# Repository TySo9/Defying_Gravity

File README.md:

# Defying_Gravity
Repository for University Kentucky Senior Capstone Design Team (Spring/Fall 2021), Defying Gravity.

## iOS App
  - Written in C# for potential multi-platform support in the future
  - Designed for iPad
  - Controls the ESP32 via Wi-Fi
  
## ESP32
  - Written in Arduino C
  - Controls motors, sensors, etc on the platform
  - Controlled by iOS App via Wi-Fi

## 3D Drawings
  - Files for the 3D printed parts of the device
     - Left Brake "Pads"
     - Right Brake "Pads"
     - Washer (?)

## 3D Drawings (KiCAD)
  - Files for PCB

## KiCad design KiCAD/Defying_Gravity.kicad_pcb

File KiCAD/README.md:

PCB Design Files for KiCAD

Because we decided to build a perfboard based on the Schematic for time, testing, and budget purposes, the PCB itself is unfinished. The Schematic, Ratnest, Part Selection, Footprint Design/Selection, etc.. is all finished. Since all the groundwork is complete, all the next person has to do is move around the footprints, connect the ratnest, and generate Gerbers. Should be quick and easy. I recommend using PCBWay to fabricate the boards.

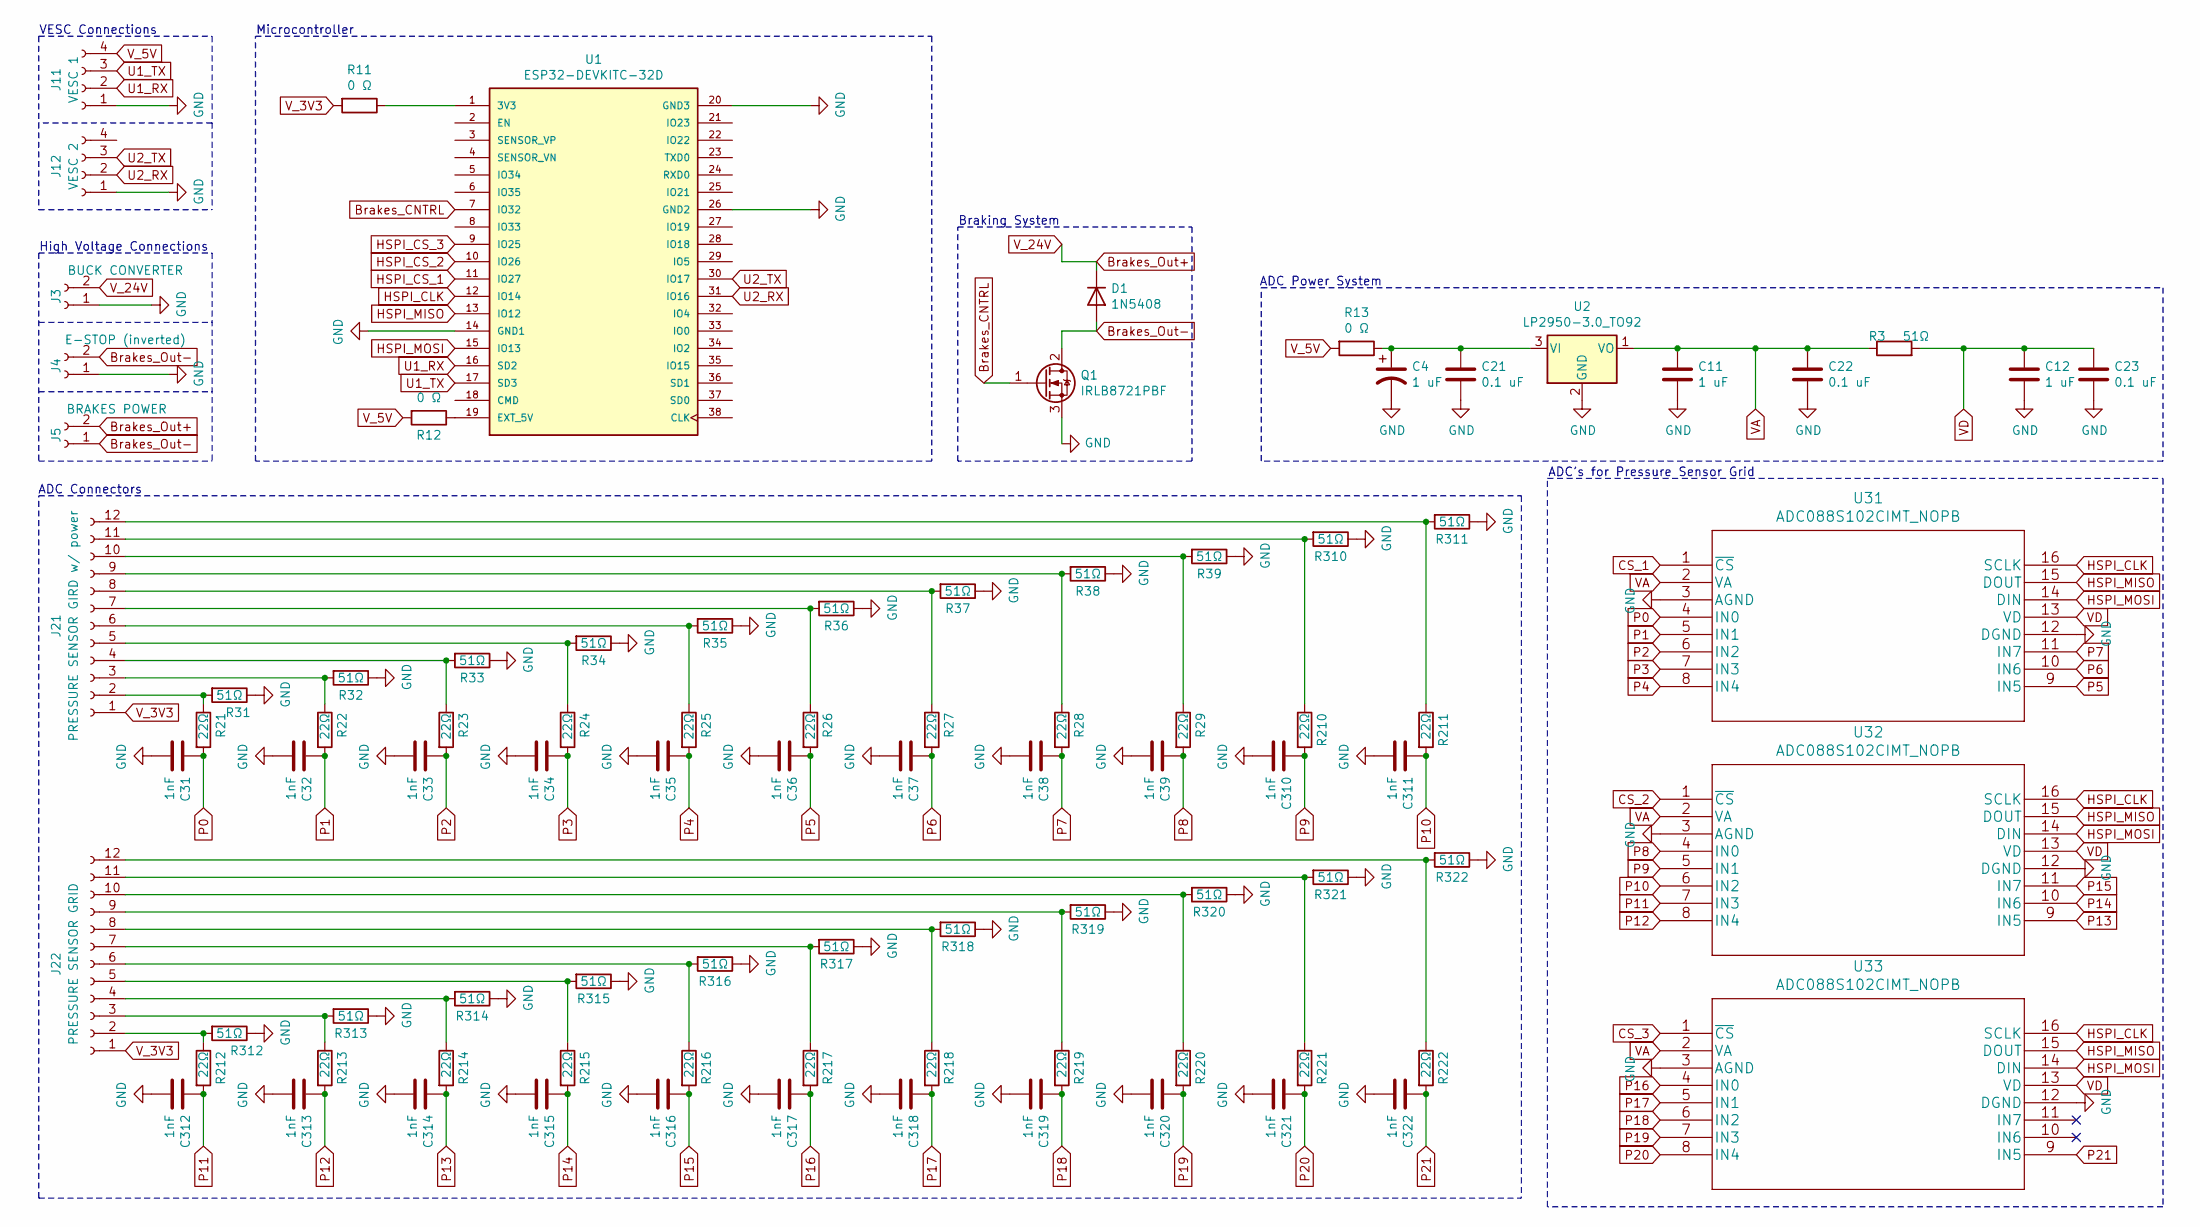
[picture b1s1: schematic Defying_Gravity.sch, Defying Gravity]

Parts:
C4, C11, C12: 1 uF; C_0805_2012Metric_Pad1.18x1.45mm_HandSolder
C21, C22, C23: 0.1 uF; C_0805_2012Metric_Pad1.18x1.45mm_HandSolder
C31, C32, C33, C34, C35, C36, C37, C38, C39, C310, C311, C312, C313, C314, C315, C316, C317, C318, C319, C320, C321, C322: 1nF; C_0805_2012Metric_Pad1.18x1.45mm_HandSolder
D1: 1N5408; D_DO-201AD_P15.24mm_Horizontal
J3: BUCK CONVERTER; TerminalBlock_Altech_AK300-2_P5.00mm
J4: E-STOP (inverted); TerminalBlock_Altech_AK300-2_P5.00mm
J5: BRAKES POWER; TerminalBlock_Altech_AK300-2_P5.00mm
J11: VESC 1; PinHeader_1x04_P2.54mm_Vertical
J12: VESC 2; PinHeader_1x04_P2.54mm_Vertical
J21: PRESSURE SENSOR GIRD w/ power; M50-3550642
J22: PRESSURE SENSOR GRID; M50-3550642
Q1: IRLB8721PBF; TO-220-3_Vertical
R3, R31, R32, R33, R34, R35, R36, R37, R38, R39, R310, R311, R312, R313, R314, R315, R316, R317, R318, R319, R320, R321, R322: 51Ω; R_0805_2012Metric_Pad1.20x1.40mm_HandSolder
R11, R12, R13: 0 Ω; R_0805_2012Metric_Pad1.20x1.40mm_HandSolder
R21, R22, R23, R24, R25, R26, R27, R28, R29, R210, R211, R212, R213, R214, R215, R216, R217, R218, R219, R220, R221, R222: 22Ω; R_0805_2012Metric_Pad1.20x1.40mm_HandSolder
U1: ESP32-DEVKITC-32D; MODULE_ESP32-DEVKITC-32D; PARTREV 4
U2: LP2950-3.0_TO92; TO-92_Inline
U31, U32, U33: ADC088S102CIMT_NOPB; ADC088S102CIMT&slash_NOPB

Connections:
Brakes_CNTRL: Q1.1 (G), U1.7 (IO32)
Brakes_Out+: D1.1 (K), J3.2, J5.2
Brakes_Out-: D1.2 (A), J4.2, J5.1, Q1.2 (D)
CS_1: U31.1 (~CS)
CS_2: U32.1 (~CS)
CS_3: U33.1 (~CS)
GND: C4.2, C11.2, C12.2, C21.2, C22.2, C23.2, C31.2, C32.2, C33.2, C34.2, C35.2, C36.2, C37.2, C38.2, C39.2, C310.2, C311.2, C312.2, C313.2, C314.2, C315.2, C316.2, C317.2, C318.2, C319.2, C320.2, C321.2, C322.2, J3.1, J4.1, J11.1, J12.1, Q1.3 (S), R31.1, R32.1, R33.1, R34.1, R35.1, R36.1, R37.1, R38.1, R39.1, R310.1, R311.1, R312.1, R313.1, R314.1, R315.1, R316.1, R317.1, R318.1, R319.1, R320.1, R321.1, R322.1, U1.14 (GND1), U1.20 (GND3), U1.26 (GND2), U2.2 (GND), U31.3 (AGND), U31.12 (DGND), U32.3 (AGND), U32.12 (DGND), U33.3 (AGND), U33.12 (DGND)
HSPI_CLK: U1.12 (IO14), U31.16 (SCLK), U32.16 (SCLK), U33.16 (SCLK)
HSPI_CS_1: U1.11 (IO27)
HSPI_CS_2: U1.10 (IO26)
HSPI_CS_3: U1.9 (IO25)
HSPI_MISO: U1.13 (IO12), U31.15 (DOUT), U32.15 (DOUT), U33.15 (DOUT)
HSPI_MOSI: U1.15 (IO13), U31.14 (DIN), U32.14 (DIN), U33.14 (DIN)
unnamed: C4.1, C21.1, R13.1, U2.3 (VI)
unnamed: J21.2, R21.1, R31.2
unnamed: J21.3, R22.1, R32.2
unnamed: J21.4, R23.1, R33.2
unnamed: J21.5, R24.1, R34.2
unnamed: J21.6, R25.1, R35.2
unnamed: J21.7, R26.1, R36.2
unnamed: J21.8, R27.1, R37.2
unnamed: J21.9, R28.1, R38.2
unnamed: J21.10, R29.1, R39.2
unnamed: J21.11, R210.1, R310.2
unnamed: J21.12, R211.1, R311.2
unnamed: J22.2, R212.1, R312.2
unnamed: J22.3, R213.1, R313.2
unnamed: J22.4, R214.1, R314.2
unnamed: J22.5, R215.1, R315.2
unnamed: J22.6, R216.1, R316.2
unnamed: J22.7, R217.1, R317.2
unnamed: J22.8, R218.1, R318.2
unnamed: J22.9, R219.1, R319.2
unnamed: J22.10, R220.1, R320.2
unnamed: J22.11, R221.1, R321.2
unnamed: J22.12, R222.1, R322.2
unnamed: R11.1, U1.1 (3V3)
unnamed: R12.1, U1.19 (EXT_5V)
P0: C31.1, R21.2, U31.4 (IN0)
P1: C32.1, R22.2, U31.5 (IN1)
P2: C33.1, R23.2, U31.6 (IN2)
P3: C34.1, R24.2, U31.7 (IN3)
P4: C35.1, R25.2, U31.8 (IN4)
P5: C36.1, R26.2, U31.9 (IN5)
P6: C37.1, R27.2, U31.10 (IN6)
P7: C38.1, R28.2, U31.11 (IN7)
P8: C39.1, R29.2, U32.4 (IN0)
P9: C310.1, R210.2, U32.5 (IN1)
P10: C311.1, R211.2, U32.6 (IN2)
P11: C312.1, R212.2, U32.7 (IN3)
P12: C313.1, R213.2, U32.8 (IN4)
P13: C314.1, R214.2, U32.9 (IN5)
P14: C315.1, R215.2, U32.10 (IN6)
P15: C316.1, R216.2, U32.11 (IN7)
P16: C317.1, R217.2, U33.4 (IN0)
P17: C318.1, R218.2, U33.5 (IN1)
P18: C319.1, R219.2, U33.6 (IN2)
P19: C320.1, R220.2, U33.7 (IN3)
P20: C321.1, R221.2, U33.8 (IN4)
P21: C322.1, R222.2, U33.9 (IN5)
U1_RX: J11.2, U1.16 (SD2)
U1_TX: J11.3, U1.17 (SD3)
U2_RX: J12.2, U1.31 (IO16)
U2_TX: J12.3, U1.30 (IO17)
VA: C11.1, C22.1, R3.1, U2.1 (VO), U31.2 (VA), U32.2 (VA), U33.2 (VA)
VD: C12.1, C23.1, R3.2, U31.13 (VD), U32.13 (VD), U33.13 (VD)
V_3V3: J21.1, J22.1, R11.2
V_5V: J11.4, R12.2, R13.2

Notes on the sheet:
VESC Connections
Microcontroller
High Voltage Connections
Braking System
ADC Power System
ADC Connectors
ADC’s for Pressure Sensor Grid

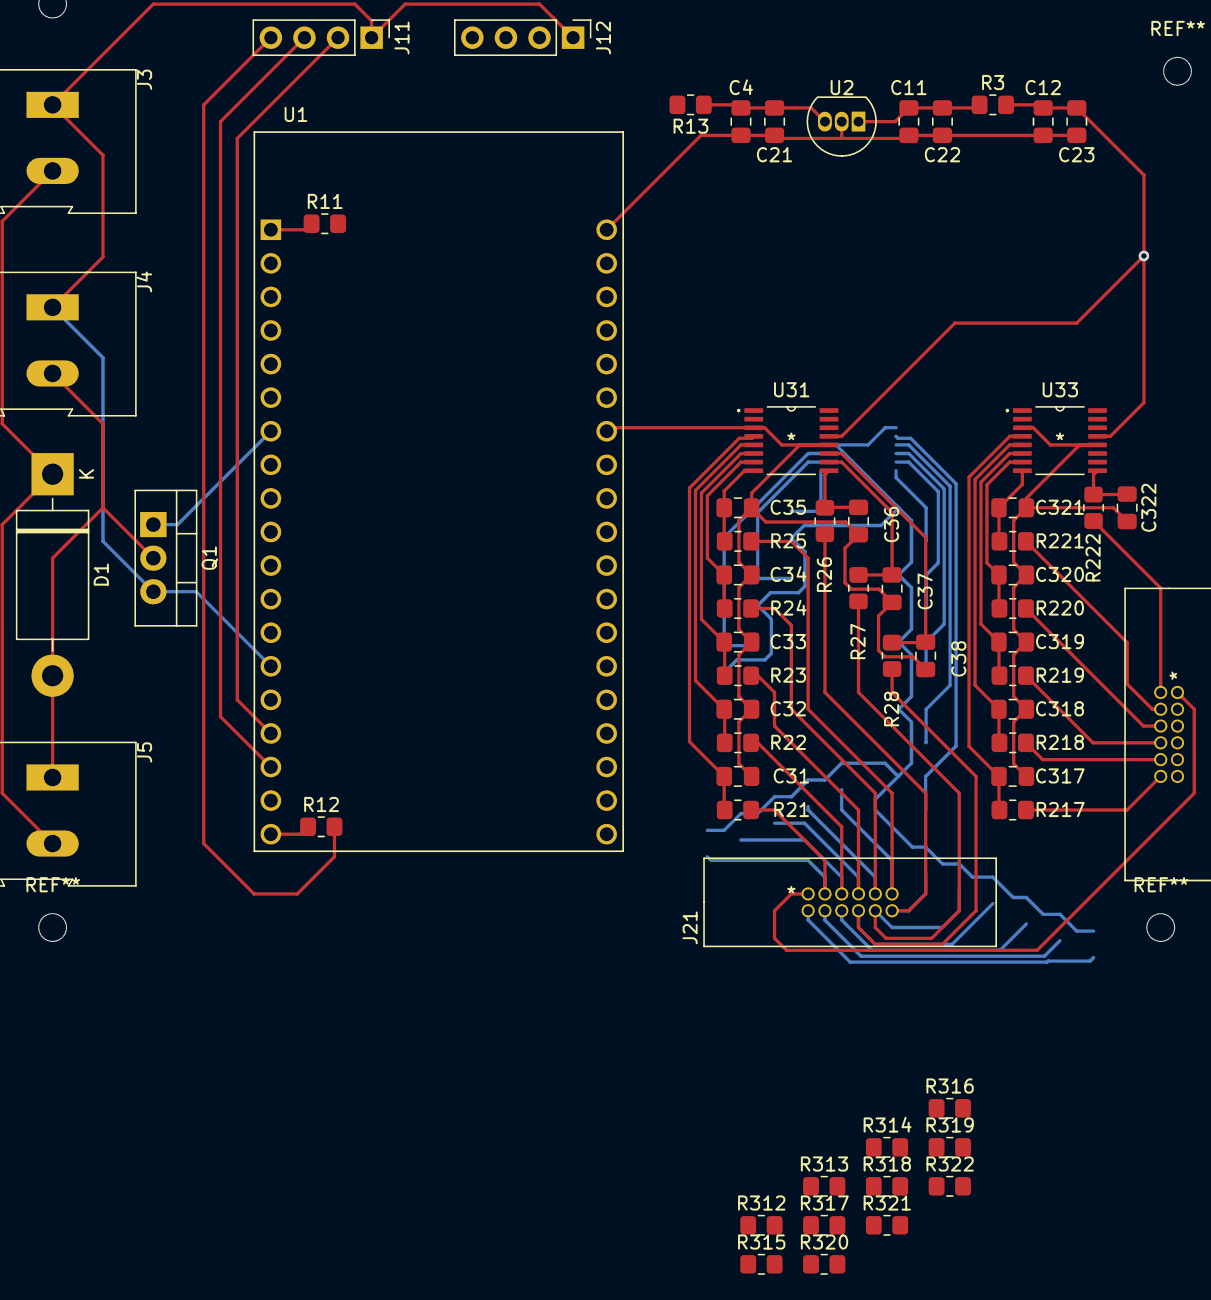
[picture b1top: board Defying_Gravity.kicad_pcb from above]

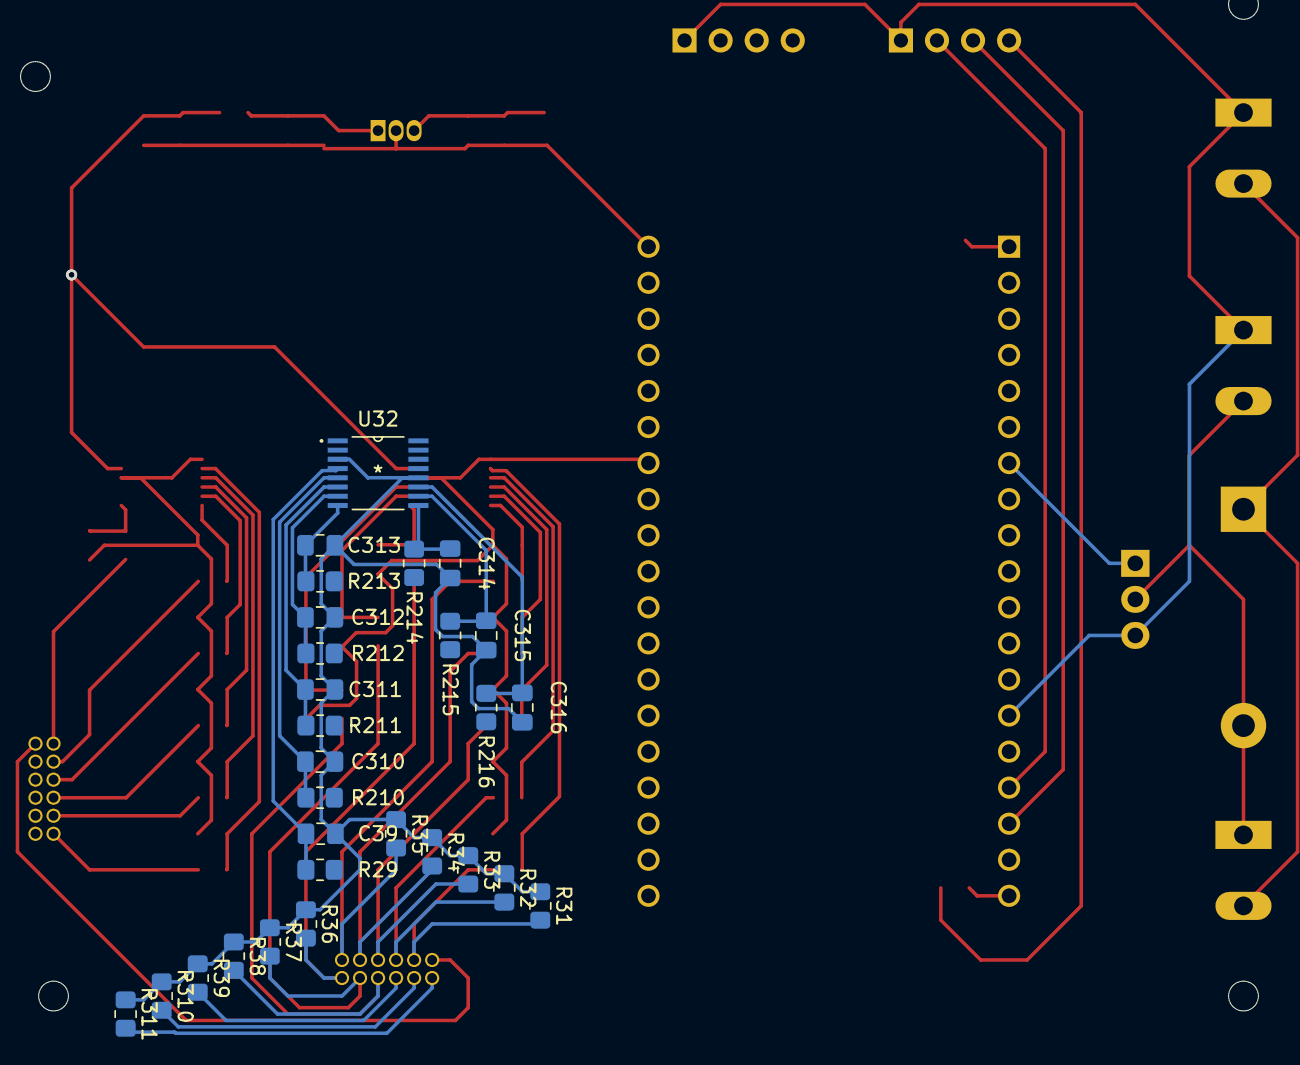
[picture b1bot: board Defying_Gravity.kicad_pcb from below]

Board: 2 copper layers, 90 parts (28 on the bottom side), 62 nets.

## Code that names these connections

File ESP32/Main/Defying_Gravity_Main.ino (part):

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int throttle = 127;

// SET UART Pins
#define U2_RX 16
#define U2_TX 17
#define U1_RX 9
#define U1_TX 10

// Brakes control pin
#define brakes_CNTRL 32

// -------------------------------------------------------------------------------------------
// VESC Control Initiation | END |
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  UART_2.setSerialPort(&Serial2);

  // Initialize Brakes Control
  pinMode(brakes_CNTRL, OUTPUT);
  digitalWrite(brakes_CNTRL, HIGH);
  
  Serial.println("BEGIN VESC CONTROL...");
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
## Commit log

2021-09-02 Rename ESP32/Adafruit_MPR121.cpp to ESP32/Library/Adafruit_MPR121.cpp
2021-09-02 Rename ESP32/Adafruit_MPR121.h to ESP32/Library/Adafruit_MPR121.h
2021-12-13 Rename ESP32/Defying_Gravity_Main.ino to ESP32/Main/Defying_Gravity_Main.ino

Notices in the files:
parts and their libraries:
Copyright 2021 Accelerated Designs. All rights reserved.
